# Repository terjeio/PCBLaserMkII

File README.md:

## BluRay Laser PCB exposer

---

### Design criteria:

160 x 100mm exposure area \(Eurocard\).
Able to render at least down to 0.25mm \(10 mil, 250um\) track/track separation.
Easy workflow.

### Vector vs. raster plotting:

Vector plotting requires parsing of a vector format to control the drive mechanism,
most PCB-design packages are able to output the design in Gerber and/or HPGL-formats.

Raster plotting is similar to inkjet printing, the laser is fired for the individual pixels.

I decided to use raster plotting since this is relatively simple to implement.

By using the belt calculator available at [buildlog.net](http://buildlog.net/cnc_laser/belt_calcs.htm) I found that
17 teeth pulleys and 8 microsteps would result in a resolution of 1195.297 steps per inch, which is pretty close to 1200 dpi \(21.250 um/step\). Near enough for hobby use, resolution may be adjusted when generating the bitmap file to match the actual resolution if a perfect match is required.

### Photosentive PCBs:

I had some blank PCBs lying around so I wanted to try Dupont Riston dry-film photoresist.
This has optimal sensitivity in the 350-380nm range, and may be exposed by 405nm as there is some sensitivity up to 450nm.
Lines and spaces achievable:
In optimized production environment: 75um/3mil
In lab environment: 50um/2mil

The (teoretical) resolution of the design is thus somewhat better than the resolution of the film.

### Workflow for KiCad EDA:

Plot the design to PDF in 1:1 format. Print resulting files via PDFCreator to PNG-format files, I use 4bpp in order to avoid artefacts in the bitmap.

### Firmware:

[Firmware](https://github.com/terjeio/PCBLaserFirmvare/) is provided for [MSP430G2553 LaunchPad](http://www.ti.com/tool/MSP-EXP430G2) or MSP430F5310 on a [custom PCB](Electrical/Controller). The MSP430F5310 is slightly faster and has more RAM, useful for buffering. It also supports adjusting the laser power via the [desktop application](https://github.com/terjeio/PCBLaserDesktopApp).

Firmware may be compiled in the [cloud](https://dev.ti.com), there is no need to install a local IDE.

### Hackaday project:

[PCB Exposer](https://hackaday.io/project/26216-pcb-exposer)

### Improvements:

A closed design with an interlocked door to block reflections from the laser. The published version is an open design, **ALWAYS** use protective eyewear when operating the exposer!

Laser cut acrylic bed? My prototype has an aluminium bed that requires access to a mill to fabricate. 

---

BOM:
<pre>
3 SC6UU 25x30x18 polymer bearing in aluminium housing
2 LM6UU 5x10x14 polymer bearing (or Oilite sintered bronze bearings)
4 6mm ground shafts, 300mm
2 3mm ground shafts or similar, 25mm for the belt idlers
1 3D printed laser carrier, FreeCAD design provided
1 diode housing 13x16x15,5
1 lens 405nm 8mm focal length?
1 405nm laser diode, 100mW
2 Nema 17 stepper motors, max 34mm long
2 17T pulleys
2 idlers to match the pulleys
  GT2 6mm belt, approx. 1m
  6mm acrylic for laser cut case, dxf-files provided
  4mm acrylic for laser cut case, dxf-files provided
1 MSP430G2553 LaunchPad or custom controller PCB (design included). Please refer to schematics for BOM for the latter.
1 laser driver PCB (design included). Please refer to schematics for BOM.
</pre>

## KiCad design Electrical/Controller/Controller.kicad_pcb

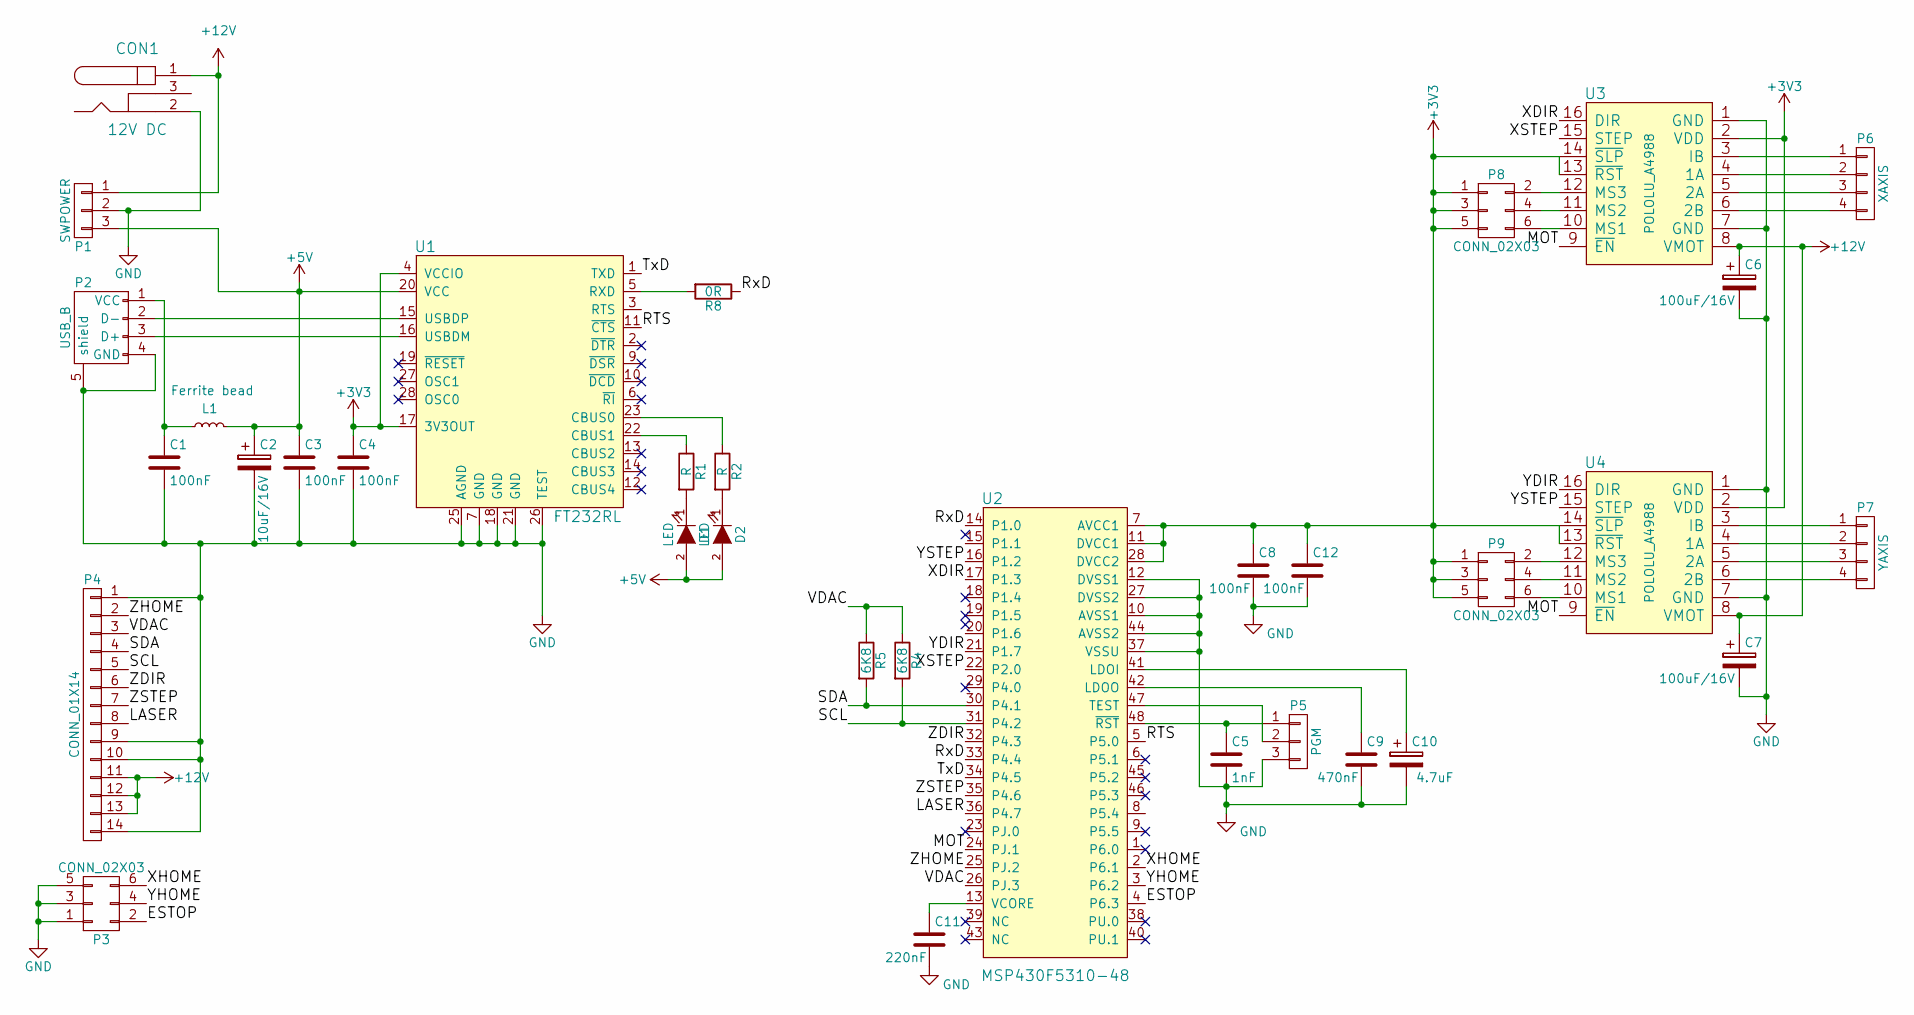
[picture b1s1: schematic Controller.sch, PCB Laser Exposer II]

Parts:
C1, C3, C4, C8, C12: 100nF; C_0805
C2: 10uF/16V; CP_Tantalum_Case-A_EIA-3216-18_Reflow
C5: 1nF; C_0805
C6, C7: 100uF/16V; CP_Radial_D8.0mm_P3.50mm
C9: 470nF; C_0805
C10: 4.7uF; CP_Tantalum_Case-A_EIA-3216-18_Reflow
C11: 220nF; C_0805
CON1: 12V DC; BARREL_JACK
D1, D2: LED; LED_1206
L1: Ferrite bead; R_0805
P1: SWPOWER; Pin_Header_Straight_1x03_Pitch2.54mm
P2: USB_B
P3, P8, P9: CONN_02X03; Pin_Header_Straight_2x03_Pitch2.54mm
P4: CONN_01X14; MOLEX_52271-1279
P5: PGM; Pin_Header_Straight_1x03_Pitch2.54mm
P6: XAXIS; Pin_Header_Straight_1x04_Pitch2.54mm
P7: YAXIS; Pin_Header_Straight_1x04_Pitch2.54mm
R1, R2: R; R_0805
R4, R5: 6K8; R_0805
R8: 0R; R_0805
U1: FT232RL; SSOP-28_5.3x10.2mm_Pitch0.65mm
U2: MSP430F5310-48; TQFP-48_7x7mm_Pitch0.5mm
U3, U4: POLOLU_A4988; Polulu_A4988

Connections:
+3V3: C4.1, C8.1, C12.1, P8.1, P8.3, P8.5, P9.1, P9.3, P9.5, U1.4 (VCCIO), U1.17 (3V3OUT), U2.7 (AVCC1), U2.11 (DVCC1), U2.28 (DVCC2), U3.2 (VDD), U3.13 (~RST), U3.14 (~SLP), U4.2 (VDD), U4.13 (~RST), U4.14 (~SLP)
+5V: C2.1, C3.1, D1.2 (A), D2.2 (A), L1.2, P1.3, U1.20 (VCC)
+12V: C6.1, C7.1, CON1.1, P1.1, P4.11, P4.12, P4.13, U3.8 (VMOT), U4.8 (VMOT)
/ESTOP: P3.2, U2.4 (P6.3)
/LASER: P4.8, U2.36 (P4.7)
/MOT: U2.24 (PJ.1), U3.9 (~EN), U4.9 (~EN)
/RTS: U1.11 (~CTS), U2.5 (P5.0)
/RxD: R8.1, U2.14 (P1.0), U2.33 (P4.4)
/SCL: P4.5, R4.2, U2.31 (P4.2)
/SDA: P4.4, R5.2, U2.30 (P4.1)
/TxD: U1.1 (TXD), U2.34 (P4.5)
/VDAC: P4.3, R4.1, R5.1, U2.26 (PJ.3)
/XDIR: U2.17 (P1.3), U3.16 (DIR)
/XHOME: P3.6, U2.2 (P6.1)
/XSTEP: U2.22 (P2.0), U3.15 (STEP)
/YDIR: U2.21 (P1.7), U4.16 (DIR)
/YHOME: P3.4, U2.3 (P6.2)
/YSTEP: U2.16 (P1.2), U4.15 (STEP)
/ZDIR: P4.6, U2.32 (P4.3)
/ZHOME: P4.2, U2.25 (PJ.2)
/ZSTEP: P4.7, U2.35 (P4.6)
GND: C1.2, C2.2, C3.2, C4.2, C5.2, C6.2, C7.2, C8.2, C9.2, C10.2, C11.2, C12.2, CON1.2, P1.2, P2.4 (GND), P2.5 (shield), P3.1, P3.3, P3.5, P4.1, P4.9, P4.10, P4.14, P5.3, U1.7 (GND), U1.18 (GND), U1.21 (GND), U1.25 (AGND), U1.26 (TEST), U2.10 (AVSS1), U2.12 (DVSS1), U2.27 (DVSS2), U2.37 (VSSU), U2.44 (AVSS2), U3.1 (GND), U3.7 (GND), U4.1 (GND), U4.7 (GND)
NC: U1.8 (NC)
unnamed: C1.1, L1.1, P2.1 (VCC)
unnamed: C5.1, P5.1, U2.48 (~RST)
unnamed: C9.1, U2.42 (LDOO)
unnamed: C10.1, U2.41 (LDOI)
unnamed: C11.1, U2.13 (VCORE)
unnamed: D1.1 (K), R1.2
unnamed: D2.1 (K), R2.2
unnamed: P5.2, U2.47 (TEST)
unnamed: P6.1, U3.3 (IB)
unnamed: P6.2, U3.4 (1A)
unnamed: P6.3, U3.5 (2A)
unnamed: P6.4, U3.6 (2B)
unnamed: P7.1, U4.3 (IB)
unnamed: P7.2, U4.4 (1A)
unnamed: P7.3, U4.5 (2A)
unnamed: P7.4, U4.6 (2B)
unnamed: P8.2, U3.12 (MS3)
unnamed: P8.4, U3.11 (MS2)
unnamed: P8.6, U3.10 (MS1)
unnamed: P9.2, U4.12 (MS3)
unnamed: P9.4, U4.11 (MS2)
unnamed: P9.6, U4.10 (MS1)
unnamed: R1.1, U1.22 (CBUS1)
unnamed: R2.1, U1.23 (CBUS0)
unnamed: R8.2, U1.5 (RXD)

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
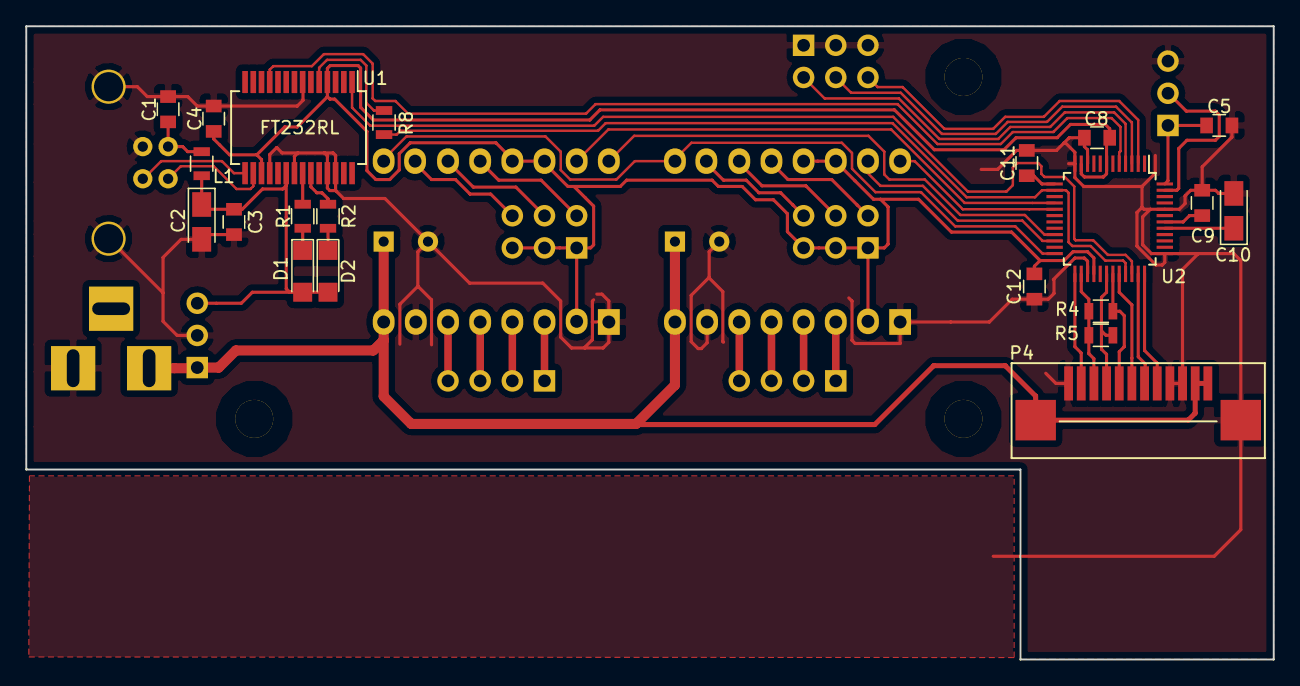
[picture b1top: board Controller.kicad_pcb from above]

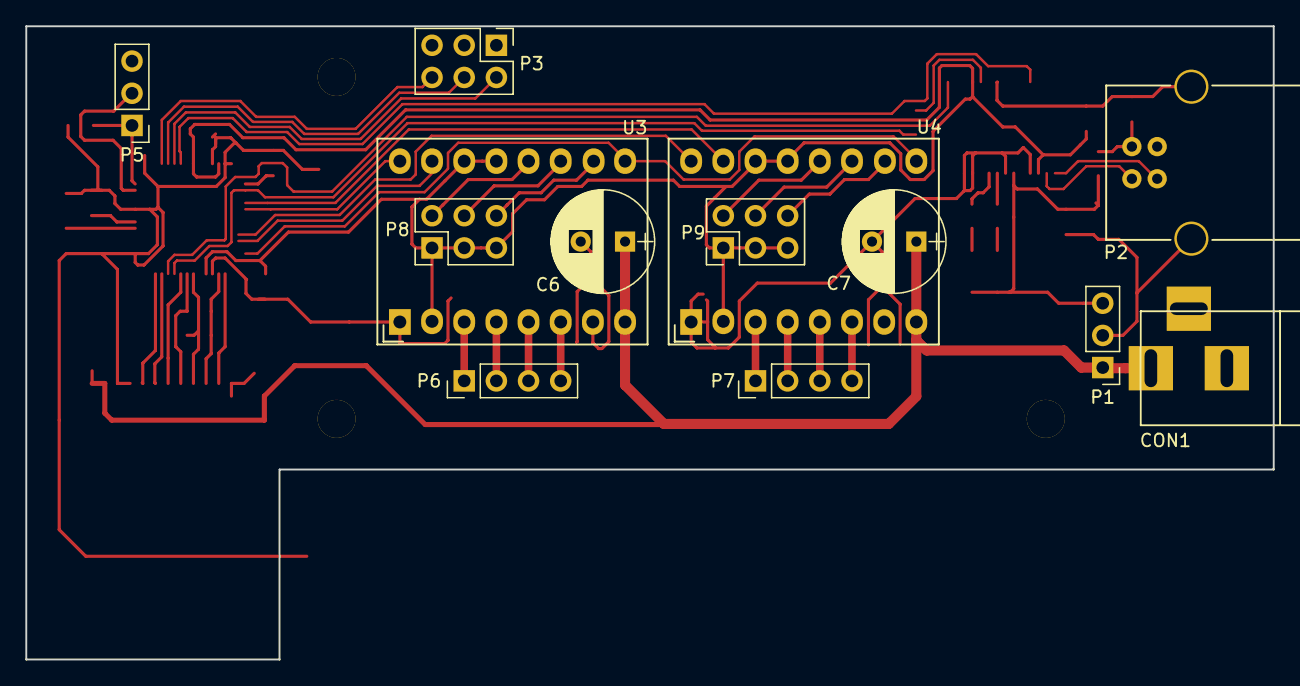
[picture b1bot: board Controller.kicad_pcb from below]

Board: 2 copper layers, 98.5 x 50.0 mm, 34 parts (13 on the bottom side), 49 nets.

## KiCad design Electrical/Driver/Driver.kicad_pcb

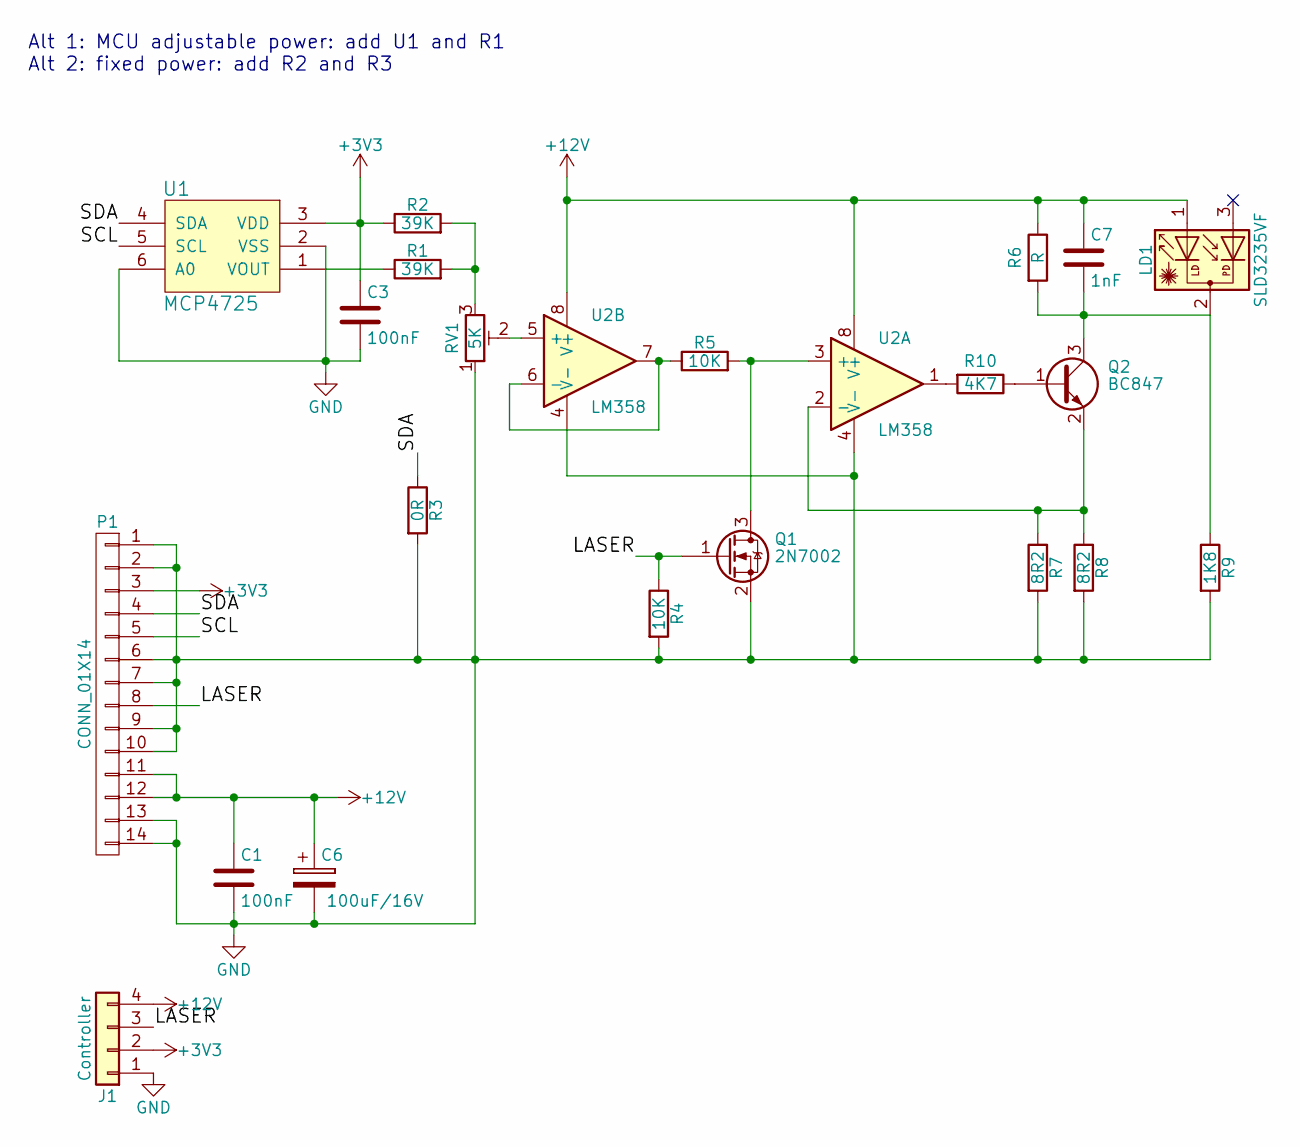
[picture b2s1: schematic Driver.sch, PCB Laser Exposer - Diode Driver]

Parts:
C1: 100nF; C_1206
C3: 100nF; C_0805
C6: 100uF/16V; CP_Elec_5x4.5
C7: 1nF; C_1206
J1: Controller; Pin_Header_Straight_1x04_Pitch2.54mm
LD1: SLD3235VF; TO-18-3_Laser_brass_host
P1: CONN_01X14; MOLEX_52271-1279
Q1: 2N7002; SOT-23
Q2: BC847; SOT-23
R1, R2: 39K; R_0805
R3: 0R; R_0805
R4, R5: 10K; R_0805
R6: R; R_0805
R7, R8: 8R2; R_1206
R9: 1K8; R_0805
R10: 4K7; R_0805
RV1: 5K; Potentiometer_Trimmer_Bourns_3296P
U1: MCP4725; SOT-23-6
U2: LM358; SOIC-8_3.9x4.9mm_Pitch1.27mm

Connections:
+3V3: C3.1, J1.2, P1.3, R2.1, U1.3 (VDD)
+12V: C1.1, C6.1, C7.1, J1.4, LD1.1, P1.11, P1.12, R6.1, U2.8 (V+)
/LASER: J1.3, P1.8, Q1.1 (G), R4.1
/SCL: P1.5, U1.5 (SCL)
/SDA: P1.4, R3.1, U1.4 (SDA)
GND: C1.2, C3.2, C6.2, J1.1, P1.1, P1.2, P1.6, P1.7, P1.9, P1.10, P1.13, P1.14, Q1.2 (S), R3.2, R4.2, R7.2, R8.2, R9.2, RV1.1, U1.2 (VSS), U1.6 (A0), U2.4 (V-)
unnamed: C7.2, LD1.2, Q2.3 (C), R6.2, R9.1
unnamed: Q1.3 (D), R5.2, U2.3 (+)
unnamed: Q2.1 (B), R10.1
unnamed: Q2.2 (E), R7.1, R8.1, U2.2 (-)
unnamed: R1.1, U1.1 (VOUT)
unnamed: R1.2, R2.2, RV1.3
unnamed: R5.1, U2.6 (-), U2.7
unnamed: R10.2, U2.1
unnamed: RV1.2, U2.5 (+)

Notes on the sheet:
Alt 1: MCU adjustable power: add U1 and R1 Alt 2: fixed power: add R2 and R3

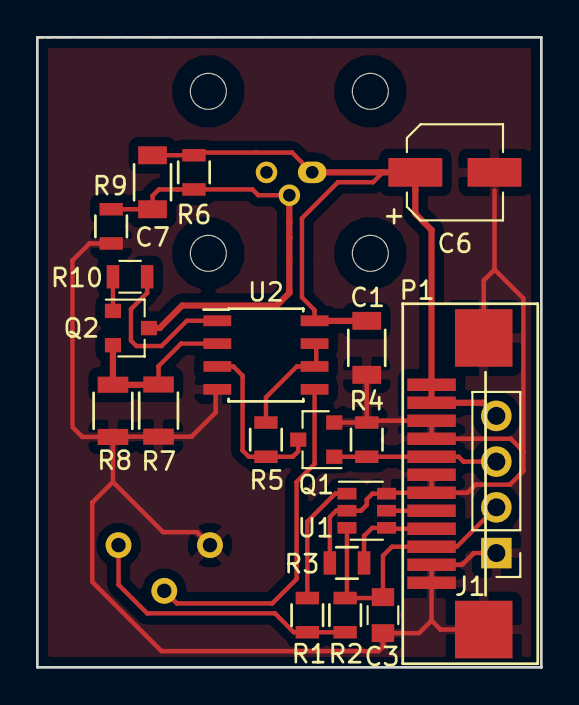
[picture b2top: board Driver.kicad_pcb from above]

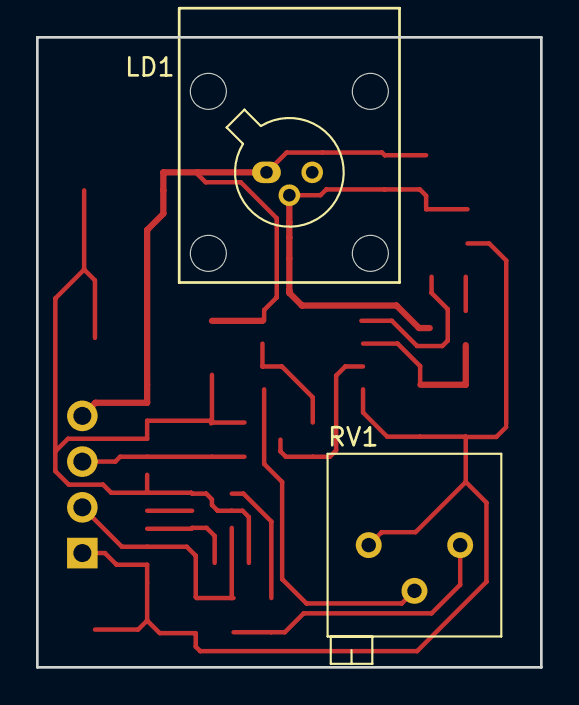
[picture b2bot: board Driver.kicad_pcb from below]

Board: 2 copper layers, 28.0 x 35.0 mm, 22 parts (2 on the bottom side), 15 nets.

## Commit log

2017-09-17 :lollipop: Added .gitattributes
2017-09-17 Initial commit of tentative design
2018-11-25 Design files used for prototype #2

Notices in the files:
Electrical/Controller/Controller.kicad_pcb:
Licensed under CERN OHL v.1.2 or later
